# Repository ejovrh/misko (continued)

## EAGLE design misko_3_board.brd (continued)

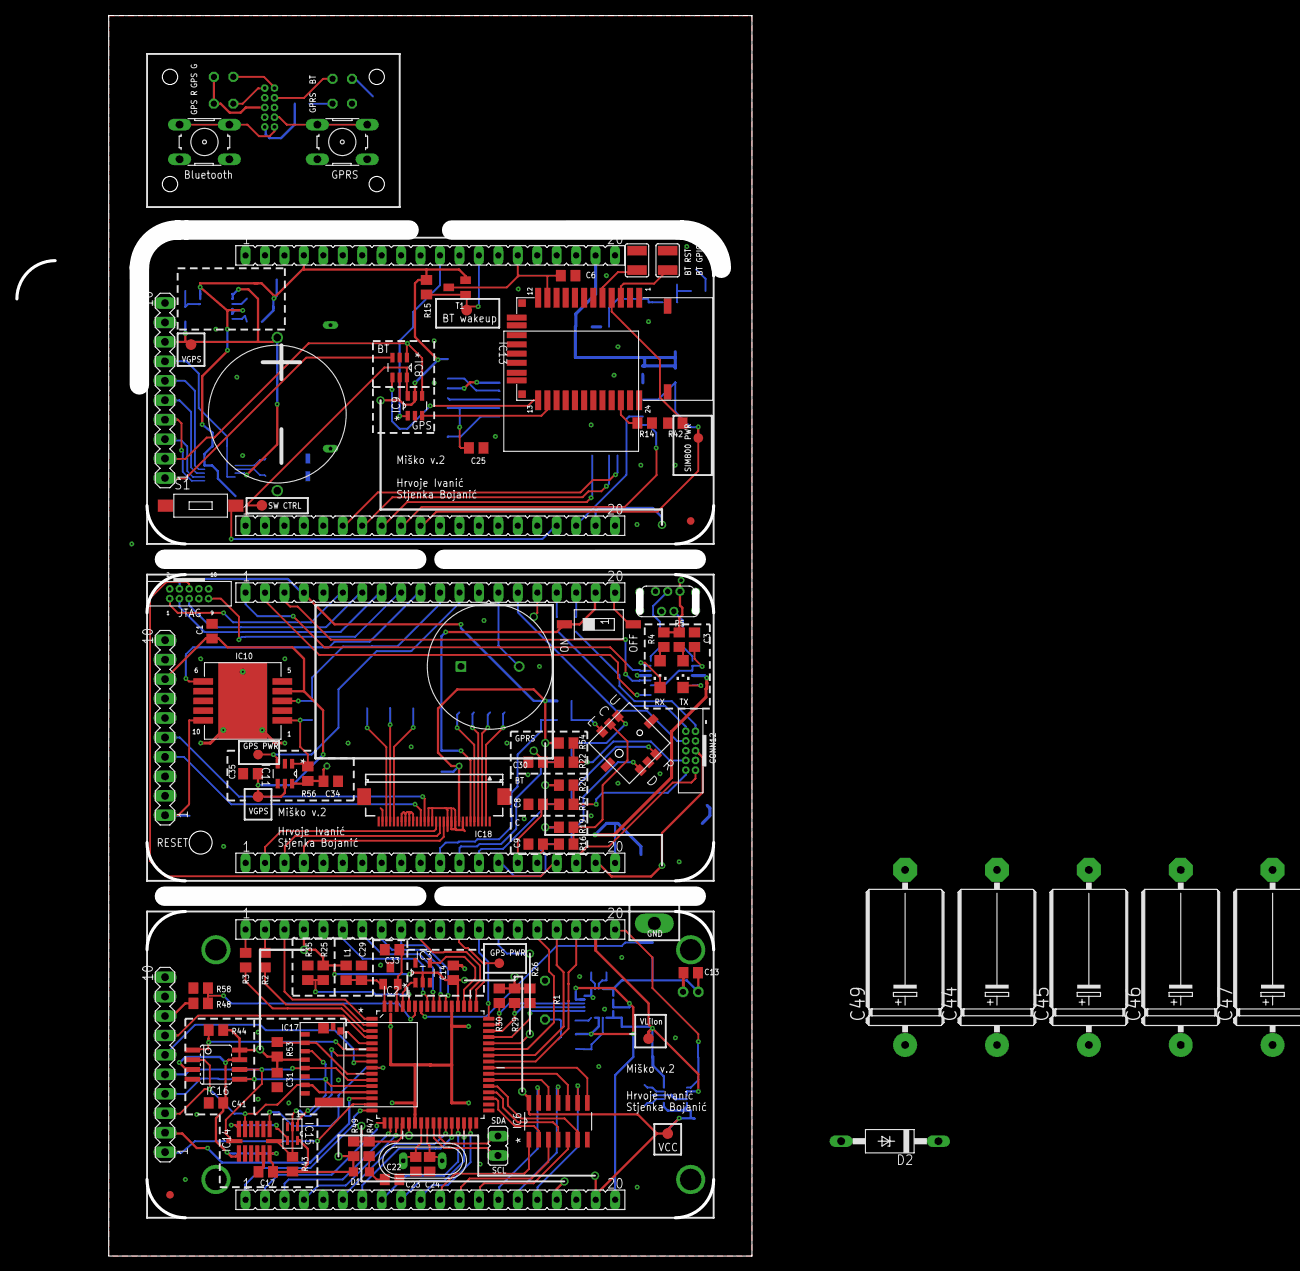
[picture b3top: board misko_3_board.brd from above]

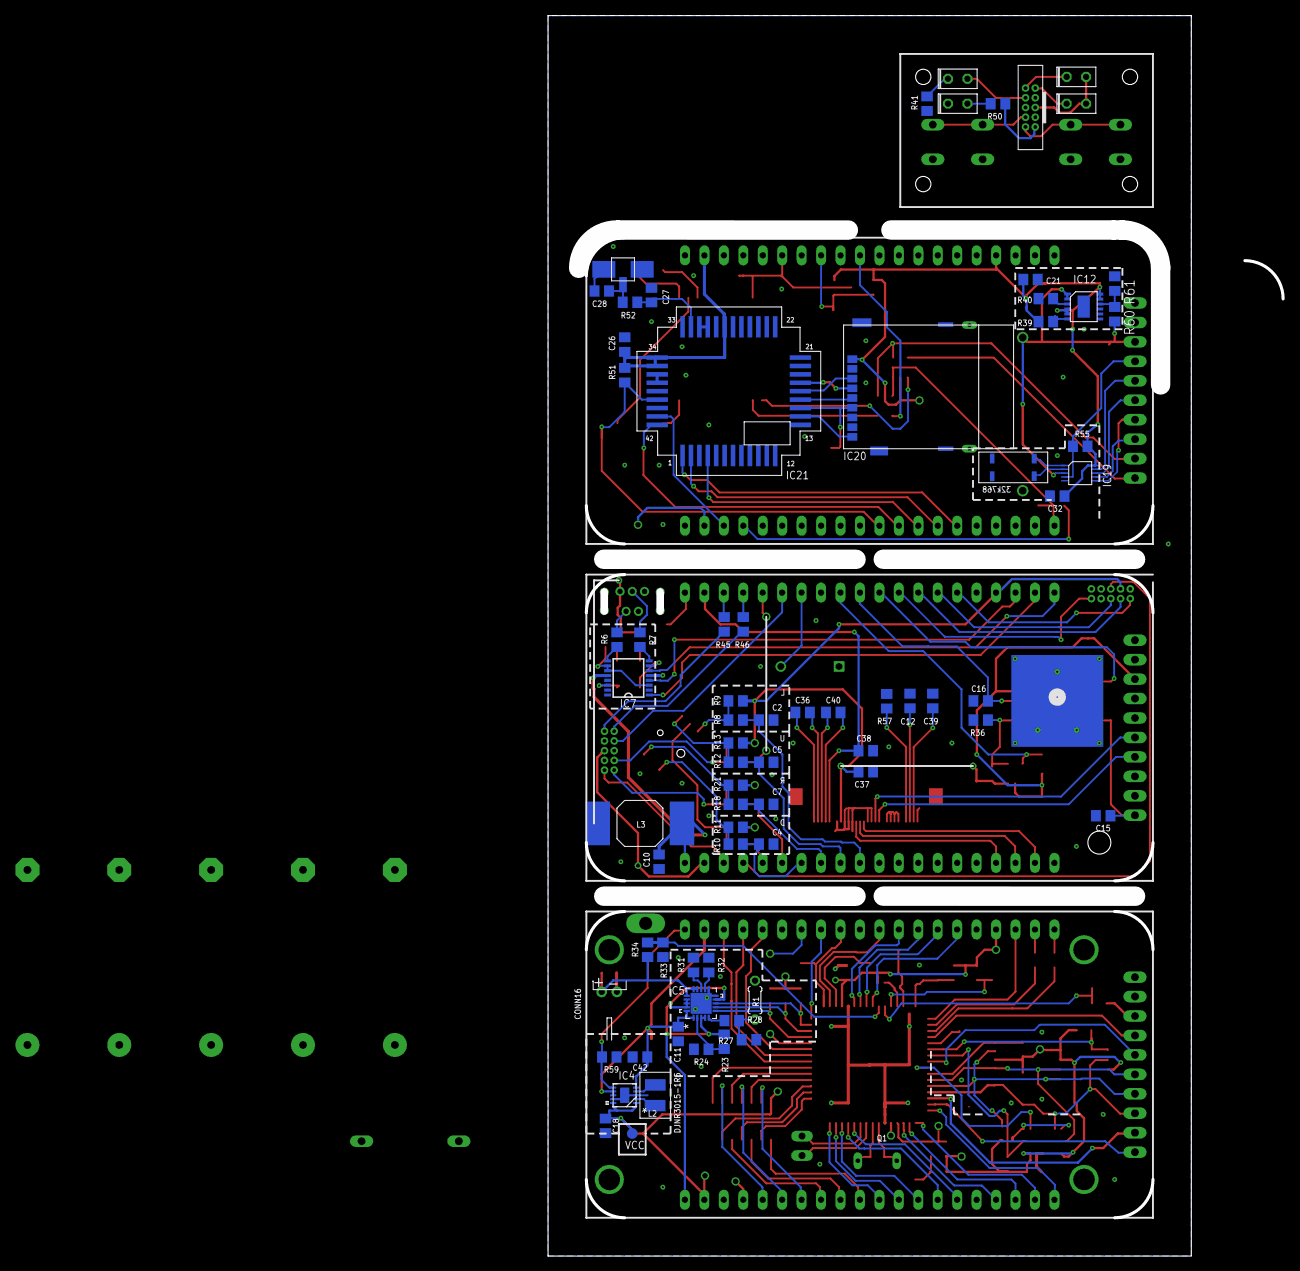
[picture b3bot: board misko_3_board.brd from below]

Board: 2 copper layers, 84.0 x 162.0 mm, 177 parts (72 on the bottom side), 131 nets.

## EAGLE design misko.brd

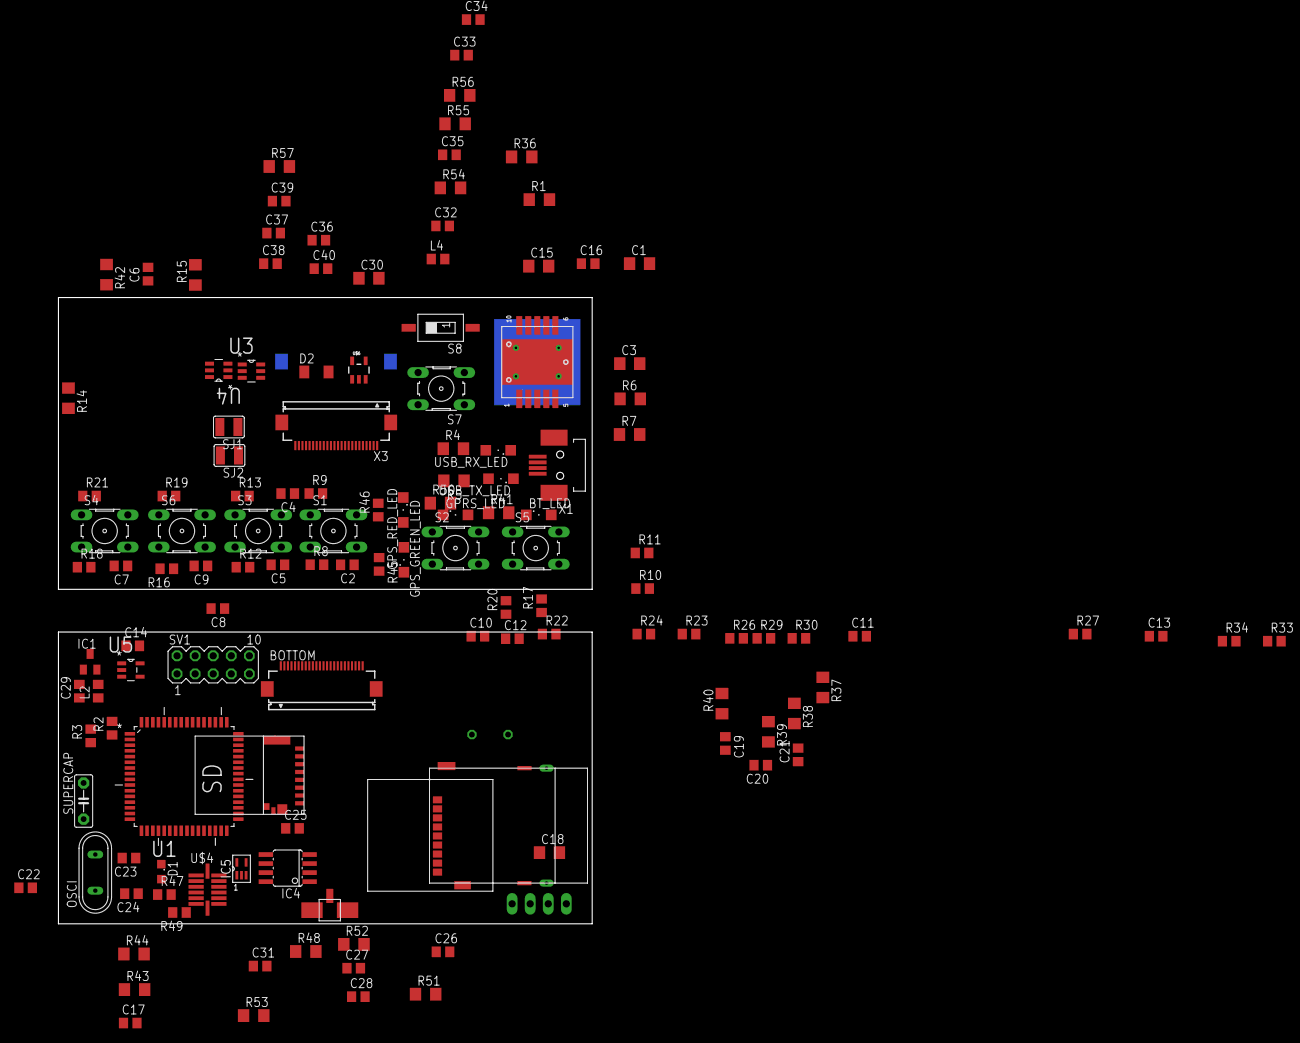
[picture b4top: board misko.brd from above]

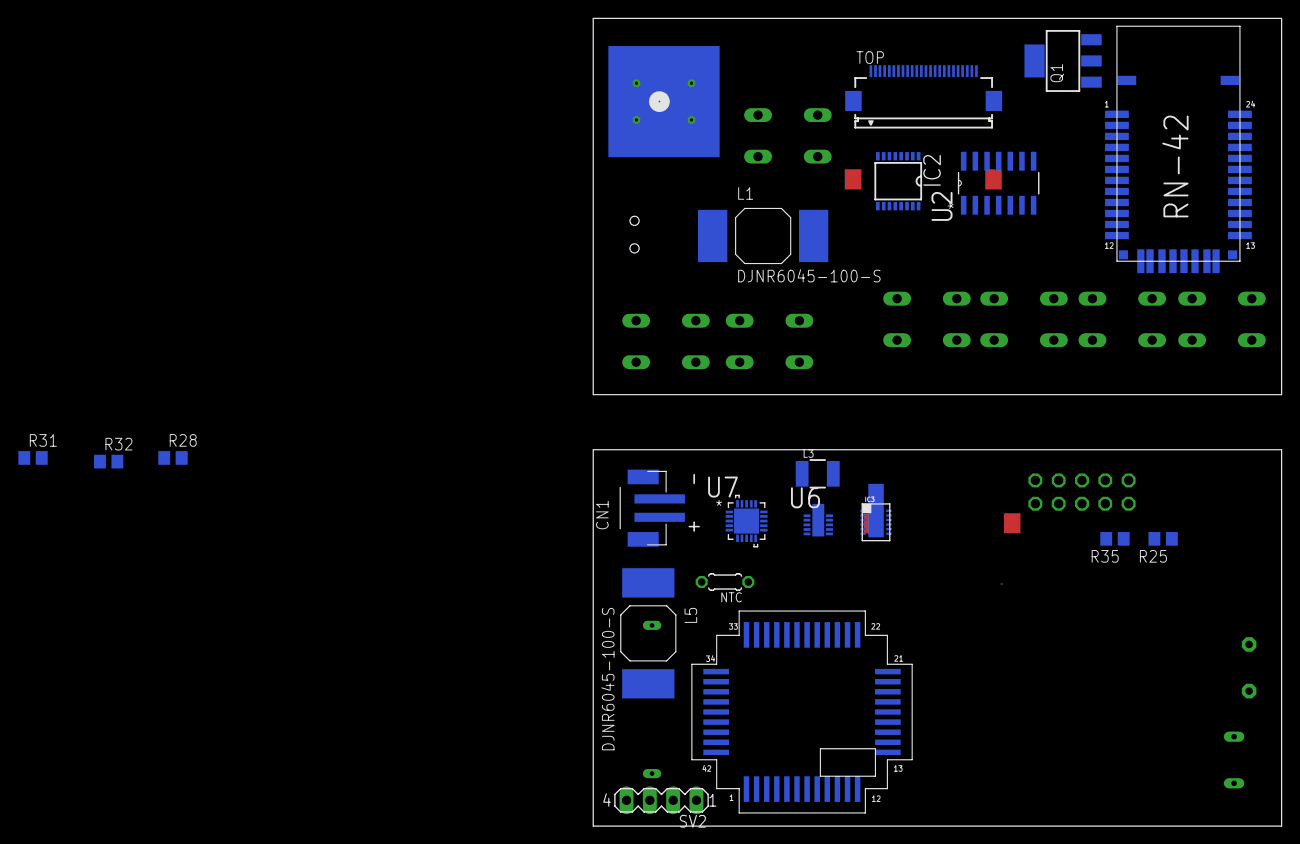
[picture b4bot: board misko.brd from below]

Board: 2 copper layers, 75.0 x 88.0 mm, 151 parts (20 on the bottom side), 127 nets, no tracks yet.

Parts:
ANT2: SMD
BOTTOM: FH12-24S-0.5SH
BT_LED: blue; SML1206
C1: 1µF; C1206
C2, C4, C5, C7, C8, C9: 0.47µF; C0805
C3: 0.1µF; C1206
C6, C10, C11, C13, C25, C27, C28, C38: 10µF; C0805
C12, C32, C33, C34, C35, C36: 4.7µF; C0805
C14, C17, C21, C22, C26, C29, C31, C37, C40: 0.1µF; C0805
C15: 18pF; C1206
C16: 18pF; C0805
C18, C30: 100nF; C1206
C19, C20: 100µF; C0805
C23, C24: 15pF; C0805
C39: 4.7µF / 25V; C0805
CN1: LiPo Battery; JST-PH-2-SMT
D1: 1N4148; D0805
D2: SOD80
GPRS_LED: red; SML1206
GPS_GREEN_LED: green; SML1206
GPS_RED_LED: red; SML1206
IC1: MC1525TT; SOT23
IC2: FT230XS; SSOP16
IC3: LTC4425; DFN12
IC4: FM25W256-SOIC; SOIC08
IC5: SOT353/5
L1, L5: DJNR6045-100-S
L2, L4: 33µH; L0805
L3: 1.5µH; MS50
NTC: 10k; 0204/5
OSCI: 8MHz; QS
Q1: FDN304P; SOT223
R1: 220; R1206
R2, R3: 3k3; R0805
R4, R5, R15, R39, R41, R48, R50, R52: 1k; R1206
R6, R7: 21; R1206
R8, R10, R12, R16, R17, R18, R26, R29, R30, R47: 47k; R0805
R9, R11, R13, R19, R20, R21, R28, R31: 1k; R0805
R14, R37, R38: 100k; R1206
R22, R33, R34: 150k; R0805
R23, R32: 100k; R0805
R24, R27, R45, R46: 270k; R0805
R25, R35: 200k; R0805
R36, R42, R43, R44, R53: 10k; R1206
R40: 46k; R1206
R49: 4.7k; R0805
R51: 47k; R1206
R54, R56: 160k; R1206
R55, R57: 910k; R1206
S1: up; B3F-10XX
S2: GPRS push; B3F-10XX
S3: right; B3F-10XX
S4: left; B3F-10XX
S5: Bluetooth; B3F-10XX
S6: down; B3F-10XX
S7: RESET; B3F-10XX
S8: POWER_SWITCH; SMS-001
SJ1, SJ2: SJW
SUPERCAP: 1F; C5B2.5
SV1: MA05-2
SV2: MA04-1
TOP: FH12-24S-0.5SH
U1: ATMEGA1281-16AU; QFP80P1600X1600X120-64N
U2: SN74HCT14DR; SOIC127P600X175-14N
U3: SN74LVC1G3157DBVR - BT switch; SOT95P280X145-6N
U4: SN74LVC1G3157DBVR - GPS switch; SOT95P280X145-6N
U5: TMP36GRTZ-REEL7; SOT95P280X145-5N
U6: TPS63030DSKT; SON50P260X260X80-11N
U7: MCP73871-2AAI/ML; QFN50P400X400X100-21N
U$1: SIM800; SIM800C
U$2: ORG1510-MK4; PACKAGE
U$3: RN-42
U$4: ADXL345; LGA14
U$5: MICROSD_SPI_MODE; MICRO_SD_CONNECTOR
U$6: V_REG_TPS61040SMD; SOT23-5
U$7: 115Q-BCA0
USB_RX_LED: yellow; SML1206
USB_TX_LED: yellow; SML1206
X1: MINI-USB_4P-32005-101; 32005-101
X3: FH12-24S-0.5SH

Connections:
5V0: C18.2, C30.2, IC2.12, L1.P$1, L5.P$2, R23.1, U7.18, U7.19
ADXL345_INT1_INTERRUPT_PIN: U1.9, U$4.INT1
ANALOG_SW_CTRL_PIN: BOTTOM.13, TOP.13, U1.18, U3.6, U4.6
ANTENNA: ANT2.SIGNAL, C28.2, R52.2
AREF: IC1.2, U1.62
AVCC: C29.2, IC1.1, L2.2, U1.64
BAT_A_PIN: R33.1, R34.2, U1.59
BLUETOOTH_RX: U3.4, U$3.UART_RX
BLUETOOTH_TX: U4.3, U$3.UART_TX
BLUETOOTH_WAKEUP_PIN: Q1.1, R15.1, U1.17
CBUS1: IC2.14, USB_TX_LED.C
CBUS2: IC2.7, USB_RX_LED.C
GND: BOTTOM.1, BOTTOM.24, C1.2, C2.1, C3.2, C4.1, C5.1, C6.1, C7.1, C8.1, C9.1, C10.1, C11.2, C12.1, C13.2, C14.2, C15.1, C16.2, C17.2, C18.1, C20.1, C21.1, C22.1, C23.1, C24.1, C25.2, C26.1, C27.1, C28.1, C29.1, C30.1, C31.2, C32.1, C33.1, C34.1, C36.1, C37.1, C38.1, C39.1, C40.1, CN1.1, GPRS_LED.C, IC1.3, IC2.5, IC2.13, IC3.GND, IC4.GND, IC5.GND, NTC.2, R14.2, R22.2, R24.2, R31.2, R32.2, R33.2, R35.2, R36.2, R41.1, R42.1, R54.1, R56.1, R57.1, S1.3, S1.4, S2.3, S2.4, S3.3, S3.4, S4.3, S4.4, S5.3, S5.4, S6.3, S6.4, S7.3, S7.4, SJ1.1, SJ2.1, SUPERCAP.1, SV1.2, SV1.10, SV2.1, TOP.1, TOP.24, U1.22, U1.53, U1.63, U2.7, U3.2, U4.2, U5.5, U6.3, U6.9, U7.10, U7.11, U$1.GND2, U$1.GND3, U$1.GND4, U$1.GND8, U$2.GND, U$3.GND1, U$3.GND2, U$3.GND3, U$3.GND4, U$3.GPIO3, U$4.GND1, U$4.GND2, U$4.GND3, U$5.GND2, U$5.GND4, U$5.POL, U$5.VSS, U$6.2, U$7.GND1, U$7.GND2, U$7.GND3, U$7.GND4, U$7.GND5, X1.4, X3.1, X3.2, X3.3, X3.6, X3.7, X3.11, X3.12, X3.24
GPS_GREEN_LED_PIN: BOTTOM.10, BOTTOM.12, R46.1, TOP.10, TOP.12, U1.42
GPS_POWER_CTL_PIN: BOTTOM.18, R1.1, R36.1, TOP.18, U1.32, U$2.ON_OFF
GPS_RED_LED_PIN: BOTTOM.9, BOTTOM.11, R45.1, TOP.9, TOP.11, U1.41
GPS_SW_SERIAL_RX: BOTTOM.19, TOP.19, U1.14, U3.1, U4.4
GPS_SW_SERIAL_TX: BOTTOM.20, C15.2, TOP.20, U1.15, U3.3, U$2.RX
GPS_TX: C16.1, U4.1, U$2.TX
GPS_WAKEUP_PIN: BOTTOM.17, TOP.17, U1.19, U$2.WAKEUP
I2C_SCL_PIN: SV2.3, U1.25
I2C_SDA_PIN: SV2.2, U1.26
IREF: R57.2, X3.21
JTAG_TCL_PIN: SV1.1, U1.57
JTAG_TDI_PIN: SV1.9, U1.54
JTAG_TDO_PIN: SV1.3, U1.55
JTAG_TMS_PIN: SV1.5, U1.56
MCP73871_CHARGE_STATUS_1_PIN: R30.2, U1.49, U7.8
MCP73871_CHARGE_STATUS_2_PIN: R29.2, U1.50, U7.7
MCP73871_POWER_GOOD_PIN: R26.2, U1.51, U7.6
MENU_BLUETOOTH_POWER_TOGGLE_PIN: BOTTOM.4, TOP.4, U1.36, U2.10
MENU_DOWN_BUTTON_PIN: BOTTOM.5, TOP.5, U1.37, U2.12
MENU_GPRS_PUSH_BUTTON_PIN: BOTTOM.7, TOP.7, U1.39, U2.4
MENU_LEFT_BUTTON_PIN: BOTTOM.3, TOP.3, U1.35, U2.8
MENU_RIGHT_BUTTON_PIN: BOTTOM.8, TOP.8, U1.40, U2.6
MENU_UP_BUTTON_PIN: BOTTOM.6, TOP.6, U1.38, U2.2
unnamed: R22.1, S8.1, U6.6
unnamed: IC2.1, R2.2
unnamed: L5.P$1, SV2.4
unnamed: R4.2, USB_RX_LED.A
unnamed: IC2.8, R7.2
unnamed: R5.1, USB_TX_LED.A
unnamed: IC2.9, R6.1
unnamed: C3.1, IC2.3, IC2.10, IC2.11
unnamed: R23.2, R24.1, U7.2
unnamed: IC2.4, R3.2
unnamed: R8.1, R9.1, S1.1, S1.2
unnamed: U7.3, U7.4, U7.9, U7.17
unnamed: R12.1, R13.1, S3.1, S3.2
unnamed: R28.1, U7.5
unnamed: R27.1, R28.2
unnamed: NTC.1, R27.2
unnamed: R10.1, R11.1, S2.1, S2.2
unnamed: R31.1, U7.13
unnamed: R32.1, U7.12
unnamed: IC3.PFI, R37.2, R38.1
unnamed: IC3.PROG, R40.2
unnamed: IC3.EN, R39.2
unnamed: IC3.PFI_RET, R37.1
unnamed: R17.1, R20.1, S5.1, S5.2
unnamed: R16.1, R19.1, S6.1, S6.2
unnamed: R18.1, R21.1, S4.1, S4.2
unnamed: C22.2, D1.A, R47.1
unnamed: C19.2, C20.2, IC3.VMID
unnamed: R42.2, U$3.GPIO7
unnamed: BT_LED.A, C6.2, Q1.2, Q1.4, U$3.VDD
unnamed: BT_LED.C, R41.2
unnamed: R14.1, U$3.GPIO4
unnamed: SJ1.2, U$3.GPIO6
unnamed: SJ2.2, U$3.RESET
unnamed: IC5.Y, U$4.SDA
unnamed: GPS_GREEN_LED.C, R46.2
unnamed: GPS_RED_LED.C, R45.2
unnamed: GPRS_LED.A, R50.2
unnamed: R50.1, U$1.NETLIGHT
unnamed: C27.2, R52.1, U$1.GSM_ANT
unnamed: U$1.GND9, U$1.GND10
unnamed: U$1.GND6, U$1.GND7
unnamed: L3.2, U6.4
unnamed: L3.1, U6.2
unnamed: D2.2, L4.1, U$6.1
unnamed: C35.1, R55.1, R56.2, U$6.3
OLED_POWER_ON-OFF: R54.2, U$6.4
PDI_UART0_CTS_PIN: BOTTOM.16, IC2.6, TOP.16, U1.1
PDI_UART0_RX_PIN: BOTTOM.14, R2.1, TOP.14, U1.2
PDI_UART0_TX_PIN: BOTTOM.15, R3.1, TOP.15, U1.3
RESET: R47.2, R49.2, S7.1, S7.2, SV1.6, U1.20
S1: C2.2, R8.2, U2.1
S2: C4.2, R10.2, U2.3
S3: C5.2, R12.2, U2.5
S4: C7.2, R18.2, U2.9
S5: C8.2, R17.2, U2.11
S6: C9.2, R16.2, U2.13
SD_CARD_DETECT_PIN: U1.16, U$5.DET
SIM800C_CTS_PIN: U1.29, U$1.UART1_CTS
SIM800C_POWER_PIN: R48.1, R51.1, U1.31, U$1.PWRKEY, U$1.VDD_EXT
SIM800C_RX_PIN: U1.27, U$1.UART1_TXD
SIM800C_STATUS_PIN: U1.30, U$1.STATUS
SIM800C_TX_PIN: U1.28, U$1.UART1_RXD
SIM_CLOCK: U$1.SIM_CLK, U$7.CLK
SIM_DATA: C25.1, U$1.SIM_DATA, U$7.I/O
SIM_DETECT: R48.2, U$1.SIM_DET, U$7.CD
SIM_RESET: U$1.SIM_RST, U$7.RST
SIM_VDD: U$1.SIM_VDD, U$7.VPP
SPI_FRAM_SS_PIN: IC4.!CS!, R44.1, U1.10
SPI_MISO_PIN: IC4.SO, U1.13, U$4.SDO, U$5.DAT0
SPI_MOSI_PIN: IC4.SI, IC5.B, U1.12, U$5.CMD, X3.14
SPI_OLED_D/C_PIN: U1.6, X3.10
SPI_OLED_RESET_PIN: U1.5, X3.9
SPI_SCK_PIN: IC4.SCK, U1.11, U$4.SCL, U$5.CLK, X3.13
SPI_SS_ADXL345_PIN: IC5.A, R43.2, U1.4, U$4.!CS!
SPI_SS_OLED_PIN: U1.7, X3.8
SPI_SS_SD_CARD_PIN: R53.1, U1.8, U$5.CD/DAT3
TMP36_SHUTDOWN_PIN: U1.48, U5.4
TMP36_VSENSE_PIN: U1.61, U5.1
USB_D+: R7.1, X1.3
USB_D-: R6.2, X1.2
VBAT: C11.1, C12.2, C26.2, R51.2, S8.2, U6.5, U6.7, U6.8, U7.1, U7.20, U$1.VBAT1, U$1.VBAT2, U$1.VRTC
VBAT+: C13.1, CN1.2, R34.1, U7.14, U7.15, U7.16
VCC: BOTTOM.2, C10.2, C14.1, C17.1, C19.1, C21.2, C31.1, C32.2, C36.2, C40.2, D1.C, GPS_GREEN_LED.A, GPS_RED_LED.A, IC3.FB, IC3.SEL, IC3.VCC1, IC3.VCC2, IC4.!HOLD!, IC4.!WP!, IC4.VCC, IC5.VCC, L2.1, L4.2, Q1.3, R9.2, R11.2, R13.2, R15.2, R19.2, R20.2, R21.2, R25.1, R26.1, R29.1, R30.1, R38.2, R39.1, R40.1, R43.1, R44.2, R49.1, R53.2, SV1.4, TOP.2, U1.21, U1.52, U2.14, U3.5, U4.5, U5.2, U6.1, U6.10, U$4.VCC, U$4.VDD, U$5.VDD, U$6.5, U$7.VCC, X3.5
VCC_SENSE_PIN: R25.2, R35.1, U1.60
VCOMH: C39.2, X3.22
VGPS: C1.1, IC3.VOUT1, IC3.VOUT2, SUPERCAP.2, U$2.VCC
VOLED: C33.2, C34.2, C35.2, C37.2, C38.2, D2.1, R55.2, X3.23
VUSB: L1.P$2, R4.1, R5.2, X1.1
XTAL1: C24.2, OSCI.1, U1.24
XTAL2: C23.2, OSCI.2, U1.23

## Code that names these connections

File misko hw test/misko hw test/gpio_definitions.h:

#ifndef GPIO_DEFINITIONS_H_
#define GPIO_DEFINITIONS_H_

#define    MCP73871_charge_status_1_pin			A,   0,   0	// MCP73871_CHARGE_STATUS_1_PIN - see MCP73871 datasheet pp. 21 for function
#define    MCP73871_charge_status_2_pin			A,   1,   1	// MCP73871_CHARGE_STATUS_2_PIN - see MCP73871 datasheet pp. 21 for function
#define    MCP73871_power_good_pin					A,   2,   2	// MCP73871_POWER_GOOD_PIN - see MCP73871 datasheet pp. 21 for function
#define    gps_green_led_pin   							A,   3,   3 // GPS_GREEN_LED_PIN - LED, GPS operation indicator
#define    gps_red_led_pin   								A,   4,   4 // GPS_RED_LED_PIN - LED, SD card operation indicator
#define    GPS_wakeup_pin   								A,   5,   5	// GPS_WAKEUP_PIN - senses device power state
#define    GPS_power_ctl_pin   							A,   6,   6	// GPS_POWER_CTL_PIN - signals a wakeup to the GPS device via the voltage supervisor; the sleep command is issued in software
#define    analog_sw_ctrl_pin   						A,   7,   7	// ANALOG_SW_CTRL_PIN - controls analog switches for BT/GPS <-> micro comm

#define    SPI_SS_FRAM_pin   								B,   0,   0	// SPI_S_FRAM_PIN - no direct pin operations advised
#define    SPI_SCK_pin   										B,   1,   1	// SPI_SCK_PIN - no direct pin operations advised
#define    SPI_MOSI_pin   									B,   2,   2	// SPI_MOSI_PIN - no direct pin operations advised
#define    SPI_MISO_pin   									B,   3,   3	// SPI_MISO_PIN - no direct pin operations advised
#define    GPS_sw_serial_rx   							B,   4,   4	// GPS_SW_SERIAL_RX - no direct pin operations advised
#define    GPS_sw_serial_tx   							B,   5,   5	// GPS_SW_SERIAL_TX - no direct pin operations advised
#define    SPI_SS_ADXL345_pin   						B,   6,   6	// SPI_SS_ADXL345_PIN - SPI ADXL345 SS
#define    SPI_OLED_a0_pin   								B,   7,   7	// SPI_OLED_D/C_PIN - OLED data/command pin (aka. a0)

#define    menu_right_button_pin						C,   0,   0	// MENU_RIGHT_BUTTON_PIN - joystick
#define    menu_left_button_pin							C,   1,   1	// MENU_LEFT_BUTTON_PIN -joystick
#define    menu_center_button_pin						C,   2,   2	// MENU_CENTER_BUTTON_PIN - joystick
#define    menu_up_button_pin								C,   3,   3	// MENU_UP_BUTTON_PIN - joystick
#define    menu_bluetooth_power_button_pin	C,   4,   4	// MENU_BLUETOOTH_POWER_BUTTON_PIN - external button
#define    menu_gprs_power_button_pin				C,   5,   5	// MENU_GPRS_POWER_BUTTON_PIN - external button, LED equipped
#define    Bluetooth_switch_pin   					C,   6,   6	// BLUETOOTH_SWITCH_PIN - BT unit main power switch
#define    Bluetooth_wakeup_pin   					C,   7,   7	// BLUETOOTH_WAKEUP_PIN - BT wake from sleep

#define    I2C_SCL_pin   										D,   0,   0	// I2C_SCL_PIN - no direct pin operations advised
#define    I2C_SDA_pin   										D,   1,   1	// I2C_SDA_PIN - no direct pin operations advised
#define    SIM800C_rx_pin   								D,   2,   2	// SIM800C_RX_PIN - UART from GPRS modem, no direct pin operations advised
#define    SIM800C_tx_pin   								D,   3,   3	// SIM800C_TX_PIN - UART to GPRS mode, no direct pin operations advised
#define    SIM800C_cts_pin   								D,   4,   4	// SIM800C_CTS_PIN - UART CTS for GPRS modem, no direct pin operations advised
#define    SIM800C_power_ctrl_pin   				D,   5,   5	//TODO SIM800C_POWER_CTRL_PIN -
#define    SIM800C_power_pin   							D,   6,   6	//TODO SIM800C_POWER_PIN -
#define    WIFI_enable_pin   								D,   7,   7	//TODO WIFI_EN_PIN -

#define    PDI_UART0_RX_pin   							E,   0,   0	// PDI_UART0_RX_PIN -
#define    PDI_UART0_TX_pin   							E,   1,   1	// PDI_UART0_TX_PIN -
#define    SD_card_detect_pin								E,   2,   2	// SD_CARD_DETECT_PIN - SD card detect
#define    SPI_SS_SD_card_pin								E,   3,   3	// SPI_SS_SD_CARD_PIN - SPI SD SS
#define    WIFI_INT_interrupt_pin						E,   4,   4	// WIFI_IRQ_PIN - interrupt sense for WiFi events
#define    SPI_SS_RTC_pin										E,   5,   5	// SPI_SS_RTC_PIN - SPI RTC SS
#define    RTC_INT_interrupt_pin						E,   6,   6	// RTC_INT_INTERRUPT_PIN - interrupt sense for RTC events
#define    ADXL345_INT1_interrupt_pin				E,   7,   7	// ADXL345_INT1_INTERRUPT_PIN - interrupt sense for accelerometer events

#define    SPI_SS_WIFI_pin									F,   0,   0	// SPI_SS_WIFI_MODULE - SPI SS for WiFi
#define    Vcc_sense_pin										F,   1,   1	// VCC_SENSE_PIN - ADC, Vcc measurement
#define    bat_A_pin												F,   2,   2	// BAT_A_PIN - ADC, Vbat measurement
#define    TMP36_Vsense_pin									F,   3,   3	// TMP36_VSENSE_PIN - ADC, temperature measurement
#define    JTAG_TCL_pin											F,   4,   4	// JTAG_TCL_PIN - no direct pin operations advised
#define    JTAG_TMS_pin											F,   5,   5	// JTAG_TMS_PIN - no direct pin operations advised
#define    JTAG_TDO_pin											F,   6,   6	// JTAG_TDO_PIN - no direct pin operations advised
#define    JTAG_TDI_pin											F,   7,   7	// JTAG_TDI_PIN - no direct pin operations advised

#define    WIFI_wake_pin										G,   0,   0	//TODO WIFI_WAKE_PIN -
#define    menu_down_button_pin							G,   1,   1	// MENU_DOWN_BUTTON_PIN - joystick
#define    Bluetooth_profile_indicator_pin	G,   2,   2	// BLUETOOTH_PROF_IND_PIN - indicates currently used bluetooth profile (BT classic vs. BLE)
#define    SPI_OLED_reset_pin								G,   3,   3	// SPI_OLED_RESET_PIN - OLED reset
#define    SPI_SS_OLED_pin									G,   4,   4	// SPI_SS_OLED_PIN - SPI OLED SS
#define    PDI_UART0_CTS_pin								G,   5,   5	// PDI_UART0_CTS_PIN -

#endif /* GPIO_DEFINITIONS_H_ */

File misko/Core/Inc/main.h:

/* USER CODE BEGIN Header */
/**
 ******************************************************************************
 * @file           : main.h
 * @brief          : Header for main.c file.
 *                   This file contains the common defines of the application.
 ******************************************************************************
 * @attention
 *
 * Copyright (c) 2024 STMicroelectronics.
 * All rights reserved.
 *
 * This software is licensed under terms that can be found in the LICENSE file
 * in the root directory of this software component.
 * If no LICENSE file comes with this software, it is provided AS-IS.
 *
 ******************************************************************************
 */

/* target board: misko POC rev.3
 *	as indicated in sch & brd files
 *
 */

/* USER CODE END Header */

/* Define to prevent recursive inclusion -------------------------------------*/
#ifndef __MAIN_H
#define __MAIN_H

#ifdef __cplusplus
extern "C" {
#endif

/* Includes ------------------------------------------------------------------*/
#include "stm32h5xx_hal.h"

/* Private includes ----------------------------------------------------------*/
/* USER CODE BEGIN Includes */
#include "linked_list.h"
/* USER CODE END Includes */

/* Exported types ------------------------------------------------------------*/
/* USER CODE BEGIN ET */

/* USER CODE END ET */

/* Exported constants --------------------------------------------------------*/
/* USER CODE BEGIN EC */
extern DMA_QListTypeDef Queue_tx;
extern DMA_QListTypeDef Queue_rx;
/* USER CODE END EC */

/* Exported macro ------------------------------------------------------------*/
/* USER CODE BEGIN EM */

/* USER CODE END EM */

/* Exported functions prototypes ---------------------------------------------*/
void Error_Handler(void);

/* USER CODE BEGIN EFP */

/* USER CODE END EFP */

/* Private defines -----------------------------------------------------------*/
#define Blue_User_Button_Pin GPIO_PIN_13
#define Blue_User_Button_GPIO_Port GPIOC
#define Blue_User_Button_EXTI_IRQn EXTI13_IRQn
#define LED_Red_Pin GPIO_PIN_0
#define LED_Red_GPIO_Port GPIOC
#define LED_Yellow_Pin GPIO_PIN_1
#define LED_Yellow_GPIO_Port GPIOC
#define GPS_WKUP_Pin GPIO_PIN_2
#define GPS_WKUP_GPIO_Port GPIOC
#define GPS_RESET_Pin GPIO_PIN_3
#define GPS_RESET_GPIO_Port GPIOC
#define ADC_VGPS_Pin GPIO_PIN_0
#define ADC_VGPS_GPIO_Port GPIOA
#define ROTARY_CH2_Pin GPIO_PIN_1
#define ROTARY_CH2_GPIO_Port GPIOA
#define SPI1_SD_CS_Pin GPIO_PIN_2
#define SPI1_SD_CS_GPIO_Port GPIOA
#define UART3_VCP_RX_Pin GPIO_PIN_3
#define UART3_VCP_RX_GPIO_Port GPIOA
#define UART3_VCP_TX_Pin GPIO_PIN_4
#define UART3_VCP_TX_GPIO_Port GPIOA
#define LED_Green_Pin GPIO_PIN_5
#define LED_Green_GPIO_Port GPIOA
#define SPI1_FRAM_CS_Pin GPIO_PIN_6
#define SPI1_FRAM_CS_GPIO_Port GPIOA
#define GPS_PWR_CTRL_Pin GPIO_PIN_4
#define GPS_PWR_CTRL_GPIO_Port GPIOC
#define ROTARY_CH1_Pin GPIO_PIN_2
#define ROTARY_CH1_GPIO_Port GPIOB
#define I2C2_SCL_Pin GPIO_PIN_10
#define I2C2_SCL_GPIO_Port GPIOB
#define CAN_STBY_Pin GPIO_PIN_12
#define CAN_STBY_GPIO_Port GPIOB
#define I2C2_SDA_Pin GPIO_PIN_13
#define I2C2_SDA_GPIO_Port GPIOB
#define UART1_TX_Pin GPIO_PIN_14
#define UART1_TX_GPIO_Port GPIOB
#define UART1_RX_Pin GPIO_PIN_15
#define UART1_RX_GPIO_Port GPIOB
#define CAN_RX_Pin GPIO_PIN_6
#define CAN_RX_GPIO_Port GPIOC
#define CAN_TX_Pin GPIO_PIN_7
#define CAN_TX_GPIO_Port GPIOC
#define Debug_Out_Pin GPIO_PIN_8
#define Debug_Out_GPIO_Port GPIOC
#define ADXL345_INT1_Pin GPIO_PIN_9
#define ADXL345_INT1_GPIO_Port GPIOC
#define ADXL345_INT1_EXTI_IRQn EXTI9_IRQn
#define SPI1_SCK_Pin GPIO_PIN_8
#define SPI1_SCK_GPIO_Port GPIOA
#define USB_FS_VBUS_Pin GPIO_PIN_9
#define USB_FS_VBUS_GPIO_Port GPIOA
#define USB_FS_DN_Pin GPIO_PIN_11
#define USB_FS_DN_GPIO_Port GPIOA
#define USB_FS_DP_Pin GPIO_PIN_12
#define USB_FS_DP_GPIO_Port GPIOA
#define SWDIO_Pin GPIO_PIN_13
#define SWDIO_GPIO_Port GPIOA
#define SWCLK_Pin GPIO_PIN_14
#define SWCLK_GPIO_Port GPIOA
#define JTDI_Pin GPIO_PIN_15
#define JTDI_GPIO_Port GPIOA
#define USB_FS_PWR_EN_Pin GPIO_PIN_10
#define USB_FS_PWR_EN_GPIO_Port GPIOC
#define SUPERCAP_DISCHARGE_Pin GPIO_PIN_11
#define SUPERCAP_DISCHARGE_GPIO_Port GPIOC
#define SD_CD_Pin GPIO_PIN_12
#define SD_CD_GPIO_Port GPIOC
#define USB_FS_OVCR_Pin GPIO_PIN_2
#define USB_FS_OVCR_GPIO_Port GPIOD
#define USB_FS_OVCR_EXTI_IRQn EXTI2_IRQn
#define SWO_Pin GPIO_PIN_3
#define SWO_GPIO_Port GPIOB
#define SPI1_MISO_Pin GPIO_PIN_4
#define SPI1_MISO_GPIO_Port GPIOB
#define SPI1_MOSI_Pin GPIO_PIN_5
#define SPI1_MOSI_GPIO_Port GPIOB
#define SPI1_ADXL345_CS_Pin GPIO_PIN_6
#define SPI1_ADXL345_CS_GPIO_Port GPIOB
#define SUPERCAP_EN_Pin GPIO_PIN_7
#define SUPERCAP_EN_GPIO_Port GPIOB
#define Anal_SW_CTRL_Pin GPIO_PIN_8
#define Anal_SW_CTRL_GPIO_Port GPIOB

/* USER CODE BEGIN Private defines */
#define SD_SPI_HANDLE hspi1
#define USE_ADXL345 1	// use the accelerometer
#define USE_FM25W256 1	// use the memory
#define USE_SD 1	// use the SD card
#define USE_ORG1510MK4 1 // use the GPS module
#define USE_LOGGER 1	// use the logger

#define OFF 0	// global device states
#define ON 1

#define ADC_CHANNELS 4	// how many ADC channels are we using
#define ADC_MEASURE_ITERATIONS 8 // average over one second (time-base is timer1 on a 125ms)

enum mj000_adcchannels
{  // order is important! - this MCU has ranking and the order of ADC channels is defined by ranking
	  Vgps,  // SuperCap voltage  - PA0
	  Vbat,  // battery voltage - nucleo CN7, pin 33
	  Temperature,  // internal temperature sensor
	  Vrefint  // internal reference voltage
};
/* USER CODE END Private defines */

#ifdef __cplusplus
}
#endif

#endif /* __MAIN_H */

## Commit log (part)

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2017-03-25 - added ADXL345 Accelerometer.lbr, WIP
2017-03-25 - added 74HCT1G32GW.lbr, WIP
2017-03-26 - changes to the libraries of multiple modules
2017-03-26 - added Molex SD-47309 SD Card Slot.lbr, WIP
2017-03-26 - added 115Q-BCA0 Micro-SIM Socket.lbr, WIP
2017-04-02 - SIM800 GPRS Module.lbr update
2017-04-02 - 115Q-BCA0 Micro-SIM Socket.lbr update
2017-04-08 - added EECRG0V105 SuperCap.lbr
2017-04-13 - updates to the library (properties of pins)
2017-04-13 - added EECS5R5H155 Supercap.pdf - removed EECRG0V105V - Supercap.pdf
2017-04-13 - dded micro joystick.lbr
2017-04-14 - minor changes to the library
2017-04-15 - correction of int7 pin (-> adxl345 int1)
2017-04-15 - progress on the battery holder
2017-04-15 - added OLED holder.dwg and stl
2017-04-16 - added DJNR3015-1R5 Inductor.lbr
2017-04-17 - final steps on 3-deck boards: copper mask, ground vias, 4th board for led/switches (to be mounted on lid)
2017-04-17 - updates on libraries (pin io vs. nc)
2017-04-18 - DRC'ed board
2017-04-20 - added DS13944U-33+RTC SPI module.pdf and its oscillator LFXTAL016178R 32.768kHz crystal.pdf
2017-05-06 - added TPS3808G33 Supervisor IC.pdf
2017-05-06 - corrected ground pads so that they get connected to pcb ground on ratnesting them in eagle
2017-05-07 - corrected names and place layers for top and bottom
2017-05-07 - DRC completed
2017-05-13 - corrected too big spatial dimensions (took 1mm off), rerouted what needed to be rerouted, ERC & DRC are error free
2017-05-21 - implemented capacitor bank for support of solar panels (see adafruits solar charger)
2017-05-25 - made wire-connected holes/traces larger
2017-05-27 - corrected position of liion bypass cap
2017-05-28 - corrected milling pattern
2017-06-11 - replaced LTC4425's Vmid capacitor divider by resistors -
2017-06-11 - replaced TH reset switch with smaller SMD part
2017-06-14 - corrected resisitor divider for LTC4425 - R60/61 now connect to Vgps (instead of Vcc)
2017-06-15 - added UB-M5BR-DM14-4D - USB B mini socket.pdf datasheet
2017-06-16 - added FERAM_GPS_LAST_GOOD_POSITION - modified once again the baud rate to 9k6
2017-06-16 - empty commit for the project file
2017-06-17 - sized up the NMEA buffer to 2048 - added DEVICE_STATISTICS_FREQUENCY define - will evenutally enable stat logging every 5s - added timer5 flags so that active elements can be moved out of the ISR -
2017-06-17 - flag_timer5_handler_execute is set by timer5 ISR; if set it does the work the ISR used to do
2017-06-18 - modified display code to make use of new ok buttons
2017-08-01 - removed bottom copper fill, not needed
2017-08-01 - corrected the size of the land pattern
2017-08-02 - converted TH connector to SMT
2017-08-02 - corrected antenna keep-out area
2017-08-03 - added holed on ground plane for better soldering & heatsink
2017-08-05 - added PB6156RSL Illuminated Tact SPST-NO switch.lbr illuminated SPST-NO tact pushbutton
2017-08-14 - added ATWINC1500-MR210PB WiFi Module.lbr and datasheet
2017-08-15 - replaced RN42 - Bluetooth Module with more modern RN4678 Bluetooth 4.2 Dual Mode Module, updated datasheets and libraries
2017-08-19 - added BOM for misko_1_board hardware
2017-08-30 - corrected name placement for R39 and R33
2017-08-30 - added 0.25mm spacing between copper fill and board edge
2017-08-31 - corrected name labeling of 5V0, VUSB, LiPo connectors at top right board edge
2017-09-08 - grounded MAX6818 !EN! pin to work properly: now key release is high, key press is low on the joystick and buttons
2017-09-08 - corrected joystick signal routing of down and right signal around holes; they had a short to ground in the rev2. layout
2017-09-11 - updated micro joystick.lbr so that tplace does not go over pads, lengthened the tplace footprint and moved a bit down towards the cpu (it stood over the board edge a little bit)
2017-09-15 - added zener protection diodes to wifi, bluetooth modules and 5v0 input
2017-09-23 - corrected values for oscillator load capacitors
2017-09-23 - added pulldown (R23) to GPS_POWER_CTL_PIN so that the receiver is turned off when micro controller resets
2017-09-27 - added UART code, tested it on both hardware UARTs
2017-09-28 - renamed SPI SS for WiFi to match the rest
2017-09-29 - added crude driver for DS1394U-33+ RTC clock - corrected FRAM SS name to SPI_SS_FRAM_pin
2017-10-01 - corrected EN pulldown resistor value to 10k
2017-10-01 - aligned tplace/bplace stuff to grid
2017-12-24 - corrected device name of TPS63031
2017-12-31 - removed UDB inductor and protection diode - added PTS1206-Series Polyfuse
2018-01-05 - centered supercap footprint
2019-01-02 - recreated epf - eagle project identifier file
2022-01-15 - submodule issues
2022-01-17 - trimmed SPI code down to one transfer function, implemented accordingly
2022-01-18 FM25W256.c/.h: - added a TODO in each file - comment changess
2022-01-18 SDCard.c/.h: - in preparation for driver development created object structure according to other similar "classes" - e.g. the accelerometer
2022-01-18 DS1394U.c: - minor comment changes
2022-01-23 - increased UART 0 and 1 RX adn TX buffers to 256 bytes
2022-01-23 in ATMega2561.c/.h: - adapted interrupt config to changed schematic INT7 became INT0, INT6 became INT1 - rewrote bit operations to use _BV() - added a timers3,4,5 and their ISRs to do POC things: pri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
    misko.c/.h:
    - added a few comments
    - flag for timer-based print control
    in main.c:
    - implemented timer-based printout of foo via UART0
    - implemented sleep code activated by accelerometer interrupt
2022-01-23 added submodules: uart, u8glib, m2tklib
2022-01-25 - created branch for stm32 development - deleted old stuff - initialized empty stm32 project for nucleo board, left all at default settings
2022-01-27 - added two missing files (uart and gpio code/headers) to base project
2022-01-27 - added missing files
2022-01-28 - added newly created files for spi and uart
2022-02-12 - removed 32kHz LSE from config since it will not be needed
2022-02-12 - activated SPI1 in interrupt mode
2022-03-06 - added signal pinning to misko.ioc
2022-03-06 in IOC: - added 2nd ADC pin, named ADC_VGPS and ADC_V3V3 - added GPIO output pins for GPS control, named accordingly
2022-03-13 in misko.ico: - defined interrupt priorities
    added GPS device driver - ORG1510.c and .h
    - adjusted rest of firmware to use above object
2024-01-15 clean blank project
2024-01-15 more tweaking
2024-01-16 - created NUCLEO-H503RB-B02 eagle library - added datasheets - added .gitignore
2024-01-16 - annotated key peripherals to documentation layer - named nets for pin indentification
2024-01-16 - added UART1 DMA config
2024-01-16 - added ADXL345 module to schematic
2024-01-17 in adxl345.c/.h: - first working version of the adxl345 driver
2024-01-17 in main.c & sch/brd: - ditched dedicated SPI CS pullup resistors and switched to stm32 built-in pullups
2024-01-18 - activated FilesX in .ioc
2024-01-18 - added SD_CD_Pin
2024-01-19 - tweaks in FileX
2024-01-25 - added fatfs code
2024-01-27 latest fatfs driver
2024-01-27 added files
2024-01-28 - reverted ffconf.h to original (except code page change) - commented out file read code
2024-01-28 - ffconf.h changes, still working
2024-01-28 - formatted code, - pulled SD CD pin low
2024-01-29 in sd.c/.h: - implemented Free() and Write() functions - moved FatFS folder into sd folder
2024-01-29 - added org1510mk4.c/.h and initialized main.c/.h to use them
2024-01-30 - removed not needed components (crystal, voltage reference, etc.) from original schematic
2024-01-31 - added MPU config for read-only register readout - configured ADC to work on timer1 CC trigger - implemented Vgps, Vbat, Vrefint and Temperature ADC measurement over a 1s average
2024-02-01 - updated ORG1510 library - added low pass filter to GPS module UART pins
2024-02-04 - peripheral init order tweak
2024-02-04 - adapted the _wait() function to wait more precisely
2024-02-05 - minor changes in preparation for parser development - implemented untested init() function
2024-02-06 in org1510mk4.c: - improved the reset power mode slightly by adding delays and shutting the NMEA burst up before init commands are issued
2024-02-07 - git-added one preferences file
2024-02-09 in org1510mk4.c: - enabled UART1 idle line interrupt
    in stm32h5xx_it.c:
    - called HAL_UART_RxCpltCallback() ( & cleared the flag) after receiving idle line interrupt
2024-02-10 language.settings.xml update
2024-02-11 in org1510mk4.c: - corrected ring buffer fill function, now the ringbuffer is getting filled correctly
2024-02-14 in org1510mk4.c: - narrowed down hardfault a little bit: changing GPS_DMA_INPUT_BUFFER_LEN from 64 to 32 seemingly makes the fault dissapear - surrounded lwrb_free and char_written code with #define 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
2024-02-14 in misko.ioc: - narrowed down priority groups from 4/0 bits to 3/1
    in org1510mk4.c:
    - fixed hard fault (was incorrect usage of lwrb read functions
    - added FIXMEs
    - extended logic for parsing a little bit
2024-02-14 in org1510mk4.c: - implemented absolutely hideous date/time/fix parsing
2024-02-15 in org1510mk4.c: - moved GGA & ZDA parsing into own functions
2024-02-16 in org1510mk4.c: - in _Parse() moved basic NMEA validity checks into uint8_t NMEA_sentence_valid(uint8_t *out, uint8_t *prase_flag)
2024-02-17 in org1510mk4.c: - restructured coord_t to coord_dd_t to match the NMEA coordinate decimal degree format (instead of h m s) - implemented coordinate loading into coord_dd_t with the help of a helper 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
2024-02-17 in org1510mk4.c/.h: - comment changes
2024-02-18 in org1510mk4.c: - corrected few issues with power state changes
    general:
    changed some fixme comments
2024-02-19 in org1510mk4.c: - consolidated each of GNGSA and GBGSV into generic parsers
2024-02-19 in org1510mk4.c: - implemented GSA "satellties used" across GP and GL talkers
2024-02-20 in org1510mk4.c/.h: - extended code for GLL parsing (not tested)
2024-02-22 in org1510mk4.c: - changed uart buffers to more meaningful names
2024-02-23 in org1510mk4.c: - improved the NMEA loader so that it returns 1 on a complete NMEA sentence load into GPS_out[], 0 otherwise - improved the code so that parsing starts if the loader exited with 1
2024-02-23 in main.c: - added back crude manual alt+0...7 module control
2024-02-24 in org1510mk4.c: - refined discharge code
2024-02-25 addition to last commit: missed some changes
2024-02-27 in misko.ioc: - moved SPI1_SD_CS from PA1 to PA2 - added timer2 rotary encoder GPIOs on PA1 and PB2 - added I2C2 in DMA mode
2024-02-29 in org1510mk4.c/.h: - fixed flapping values for GSVs after id 4 (msgs 2 and 3) - fixed zeroing of alm and eph fields if a PRN is/becomes zero
    in stm32h5xx_it.c:
    - added flag setting of once per 10s for almanac/ephemeris query
2024-03-02 in misko.ioc/main.c: - configured RTC to start with the same date/time settings the GPS module puts out, i.e. start of the GPS week in 1980
2024-03-05 in org1510mk4.c/.h: - moved date & time into time_t and date_t structs - adapted NMEA parsers to use said structs - corrected preprocessor defines
    in timehelper.c:
    - simplified date & time set to use above structs
2024-09-15 in sch & brd: - changed hierarchical module names so that board components have shorter names (GPS subsystem stuff) - added CAN infra. components to sch
2024-09-15 - added CAN_STBY GPIO pin for TCAN 334 control
2024-09-20 yet another IDE upgrade
2024-10-12 - corrected timer1 to have a 125ms interrupt period (measured) vs. calculated
